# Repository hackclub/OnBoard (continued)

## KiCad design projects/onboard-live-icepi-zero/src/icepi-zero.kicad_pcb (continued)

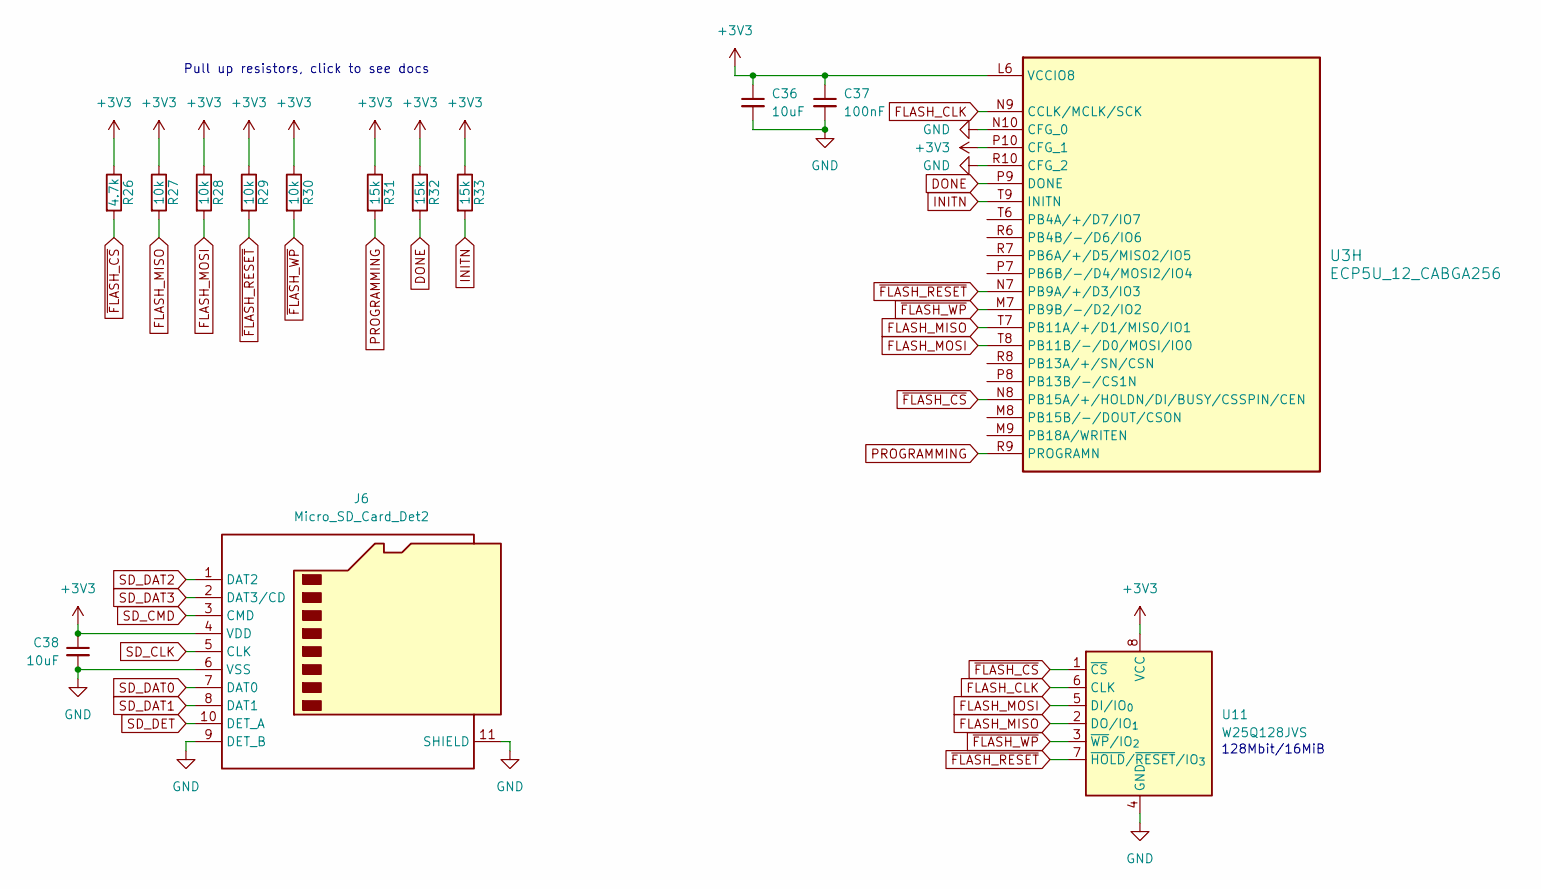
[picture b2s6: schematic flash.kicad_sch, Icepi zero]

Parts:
C36, C38: 10uF; C_0603_1608Metric
C37: 100nF; C_0402_1005Metric; JLCPCB Part # C307331
J6: Micro_SD_Card_Det2; microSD_HC_SOFNG_TF-008; JLCPCB Part # C428465
R26: 4.7k; R_0402_1005Metric; JLCPCB Part # C25900
R27, R28, R29, R30: 10k; R_0402_1005Metric; JLCPCB Part # C25744
R31, R32, R33: 15k; R_0402_1005Metric; JLCPCB Part # C25756
U3: ECP5U_12_CABGA256; BGA-256_14.0x14.0mm_Layout16x16_P0.8mm_Ball0.45mm_Pad0.32mm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; JLCPCB Part # C1521614
U11: W25Q128JVS; SOIC-8_5.3x5.3mm_P1.27mm; JLCPCB Part # C97521

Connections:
+3V3: C36.1, C37.1, C38.1, J6.4 (VDD), R26.1, R27.1, R28.1, R29.1, R30.1, R31.1, R32.1, R33.1, U3.L6 (VCCIO8), U3.P10 (CFG_1), U11.8 (VCC); also elsewhere on the board
DONE: R32.2, U3.P9 (DONE)
FLASH_CLK: U3.N9 (CCLK/MCLK/SCK), U11.6 (CLK)
FLASH_MISO: R27.2, U3.T7 (PB11A/+/D1/MISO/IO1), U11.2 (DO/IO_{1})
FLASH_MOSI: R28.2, U3.T8 (PB11B/-/D0/MOSI/IO0), U11.5 (DI/IO_{0})
GND: C36.2, C37.2, C38.2, J6.6 (VSS), J6.9 (DET_B), J6.11 (SHIELD), U3.N10 (CFG_0), U3.R10 (CFG_2), U11.4 (GND); also elsewhere on the board
INITN: R33.2, U3.T9 (INITN)
PROGRAMMING: R31.2, U3.R9 (PROGRAMN)
SD_CLK: J6.5 (CLK); also elsewhere on the board
SD_CMD: J6.3 (CMD); also elsewhere on the board
SD_DAT0: J6.7 (DAT0); also elsewhere on the board
SD_DAT1: J6.8 (DAT1); also elsewhere on the board
SD_DAT2: J6.1 (DAT2); also elsewhere on the board
SD_DAT3: J6.2 (DAT3/CD); also elsewhere on the board
SD_DET: J6.10 (DET_A); also elsewhere on the board
~FLASH_CS: R26.2, U3.N8 (PB15A/+/HOLDN/DI/BUSY/CSSPIN/CEN), U11.1 (~CS)
~FLASH_RESET: R29.2, U3.N7 (PB9A/+/D3/IO3), U11.7 (~HOLD/~RESET/IO_{3})
~FLASH_WP: R30.2, U3.M7 (PB9B/-/D2/IO2), U11.3 (~WP/IO_{2})

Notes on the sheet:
128Mbit/16MiB
Pull up resistors, click to see docs

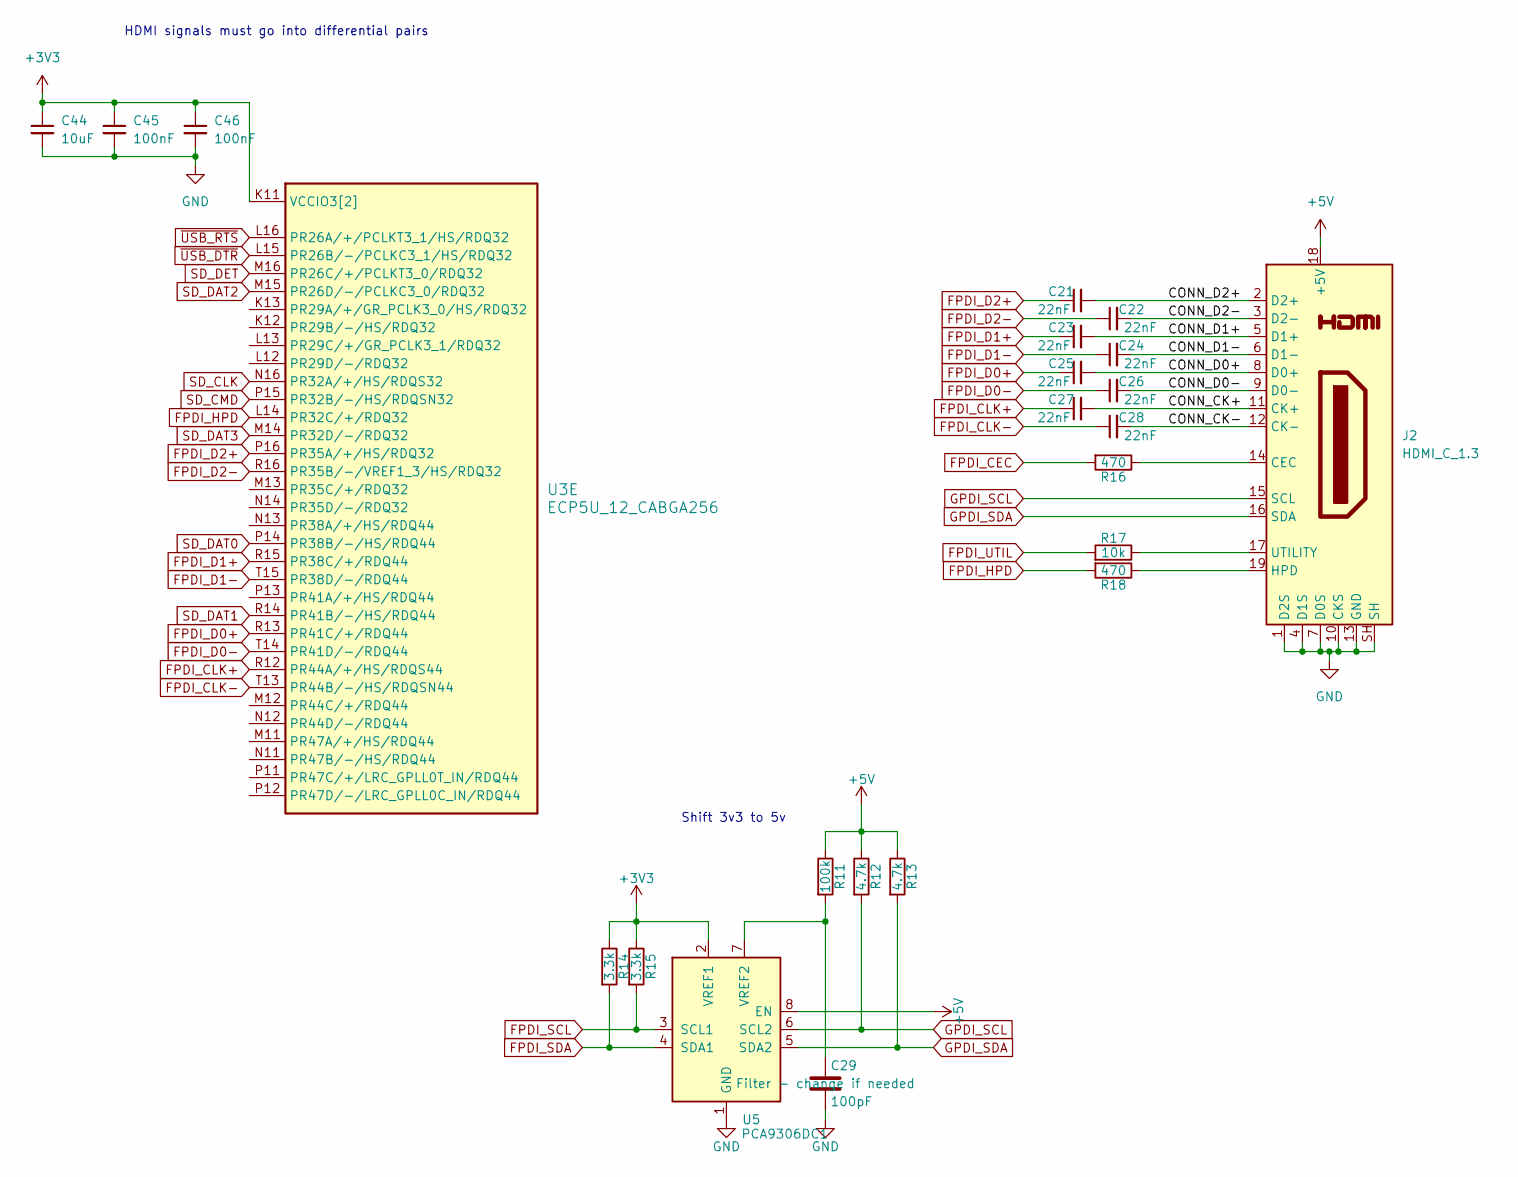
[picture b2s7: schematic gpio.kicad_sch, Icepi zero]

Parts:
C21, C22, C23, C24, C25, C26, C27, C28: 22nF; C_0402_1005Metric; JLCPCB Part # C1532
C29: 100pF; C_0402_1005Metric; JLCPCB Part # C1546
C44: 10uF; C_0603_1608Metric
C45, C46: 100nF; C_0402_1005Metric; JLCPCB Part # C307331
J2: HDMI_C_1.3; XKB Connection A71-05H4-111N1; JLCPCB Part # C2682170
R11: 100k; R_0402_1005Metric; JLCPCB Part # C25741
R12, R13: 4.7k; R_0402_1005Metric; JLCPCB Part # C25900
R14, R15: 3.3k; R_0402_1005Metric; JLCPCB Part # C25890
R16, R18: 470; R_0402_1005Metric; JLCPCB Part # C25117
R17: 10k; R_0402_1005Metric; JLCPCB Part # C25744
U3: ECP5U_12_CABGA256; BGA-256_14.0x14.0mm_Layout16x16_P0.8mm_Ball0.45mm_Pad0.32mm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; JLCPCB Part # C1521614
U5: PCA9306DC1; VSSOP-8_2.3x2mm_P0.5mm; JLCPCB Part # C129510

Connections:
+3V3: C44.1, C45.1, C46.1, R14.1, R15.1, U3.K11 (VCCIO3[2]), U3.L11 (VCCIO3[2]), U5.2 (VREF1); also elsewhere on the board
+5V: J2.18 (+5V), R11.1, R12.1, R13.1, U5.8 (EN); also elsewhere on the board
/GPIO/CONN_CK+: C27.2, J2.11 (CK+)
/GPIO/CONN_CK-: C28.2, J2.12 (CK-)
/GPIO/CONN_D0+: C25.2, J2.8 (D0+)
/GPIO/CONN_D0-: C26.2, J2.9 (D0-)
/GPIO/CONN_D1+: C23.2, J2.5 (D1+)
/GPIO/CONN_D1-: C24.2, J2.6 (D1-)
/GPIO/CONN_D2+: C21.2, J2.2 (D2+)
/GPIO/CONN_D2-: C22.2, J2.3 (D2-)
FPDI_CEC: R16.2; also elsewhere on the board
FPDI_CLK+: C27.1, U3.R12 (PR44A/+/HS/RDQS44)
FPDI_CLK-: C28.1, U3.T13 (PR44B/-/HS/RDQSN44)
FPDI_D0+: C25.1, U3.R13 (PR41C/+/RDQ44)
FPDI_D0-: C26.1, U3.T14 (PR41D/-/RDQ44)
FPDI_D1+: C23.1, U3.R15 (PR38C/+/RDQ44)
FPDI_D1-: C24.1, U3.T15 (PR38D/-/RDQ44)
FPDI_D2+: C21.1, U3.P16 (PR35A/+/HS/RDQ32)
FPDI_D2-: C22.1, U3.R16 (PR35B/-/VREF1_3/HS/RDQ32)
FPDI_HPD: R18.2, U3.L14 (PR32C/+/RDQ32)
FPDI_SCL: R15.2, U5.3 (SCL1); also elsewhere on the board
FPDI_SDA: R14.2, U5.4 (SDA1); also elsewhere on the board
FPDI_UTIL: R17.2; also elsewhere on the board
GND: C29.2, C44.2, C45.2, C46.2, J2.1 (D2S), J2.4 (D1S), J2.7 (D0S), J2.10 (CKS), J2.13 (GND), J2.SH, U5.1 (GND); also elsewhere on the board
GPDI_SCL: J2.15 (SCL), R12.2, U5.6 (SCL2)
GPDI_SDA: J2.16 (SDA), R13.2, U5.5 (SDA2)
unnamed: J2.14 (CEC), R16.1
unnamed: J2.19 (HPD), R18.1
unnamed: J2.17 (UTILITY), R17.1
unnamed: C29.1, R11.2, U5.7 (VREF2)
SD_CLK: U3.N16 (PR32A/+/HS/RDQS32); also elsewhere on the board
SD_CMD: U3.P15 (PR32B/-/HS/RDQSN32); also elsewhere on the board
SD_DAT0: U3.P14 (PR38B/-/HS/RDQ44); also elsewhere on the board
SD_DAT1: U3.R14 (PR41B/-/HS/RDQ44); also elsewhere on the board
SD_DAT2: U3.M15 (PR26D/-/PCLKC3_0/RDQ32); also elsewhere on the board
SD_DAT3: U3.M14 (PR32D/-/RDQ32); also elsewhere on the board
SD_DET: U3.M16 (PR26C/+/PCLKT3_0/RDQ32); also elsewhere on the board
~USB_DTR: U3.L15 (PR26B/-/PCLKC3_1/HS/RDQ32); also elsewhere on the board
~USB_RTS: U3.L16 (PR26A/+/PCLKT3_1/HS/RDQ32); also elsewhere on the board

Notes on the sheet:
Shift 3v3 to 5v
HDMI signals must go into differential pairs

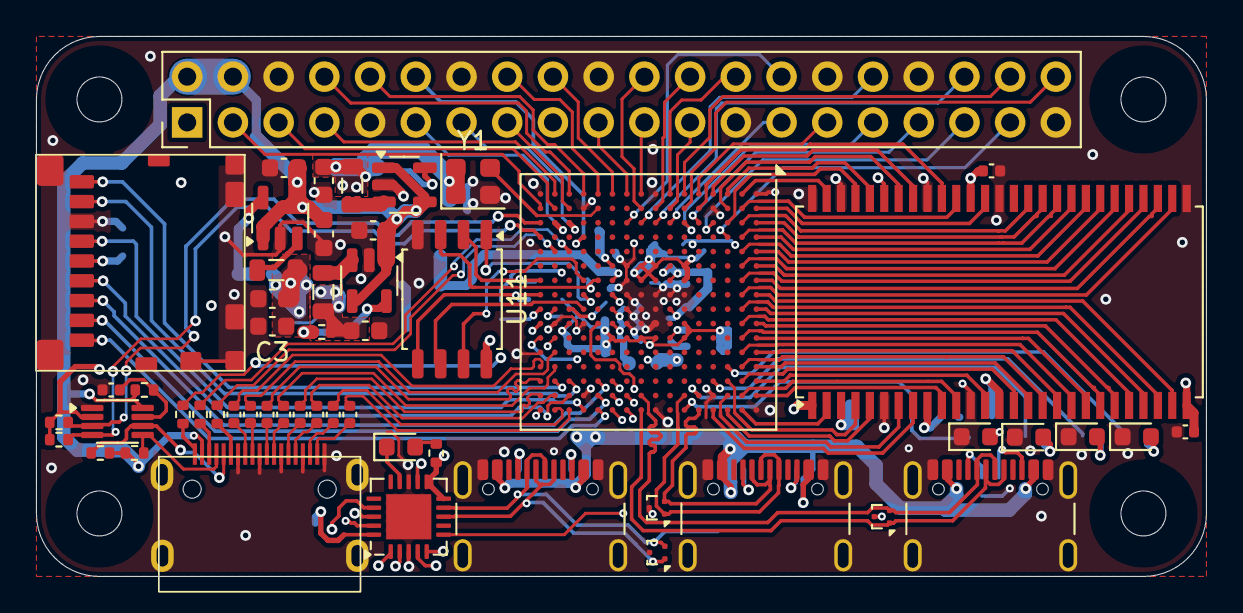
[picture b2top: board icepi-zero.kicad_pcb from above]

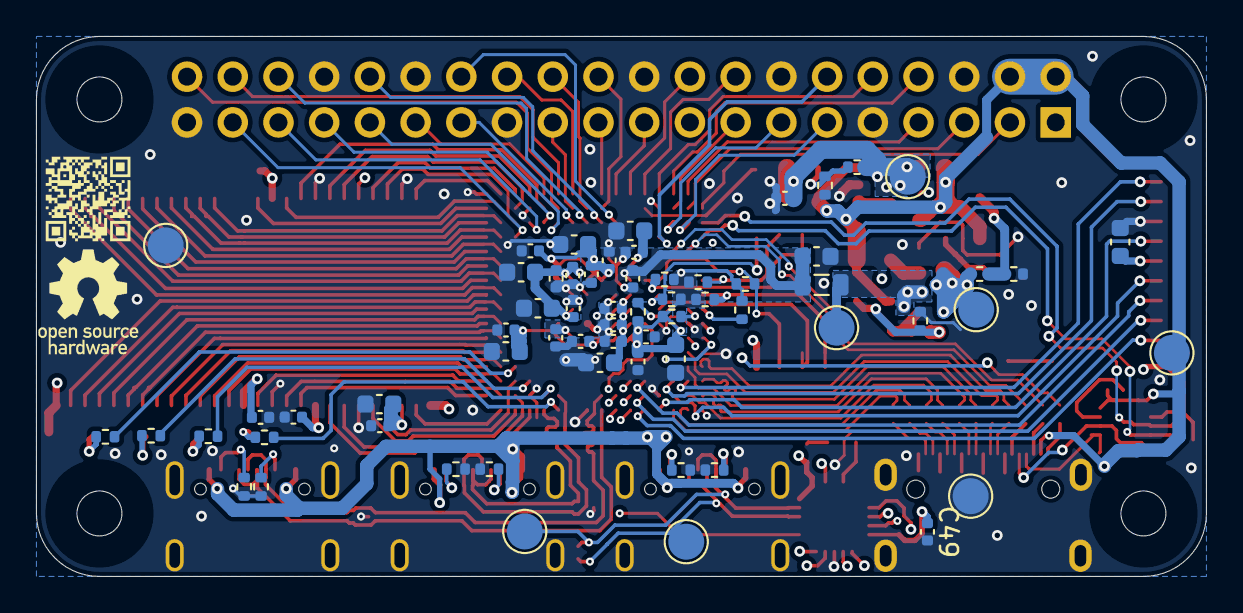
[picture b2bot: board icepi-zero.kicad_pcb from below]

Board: 4 copper layers, 65.0 x 30.0 mm, 121 parts (63 on the bottom side), 154 nets.

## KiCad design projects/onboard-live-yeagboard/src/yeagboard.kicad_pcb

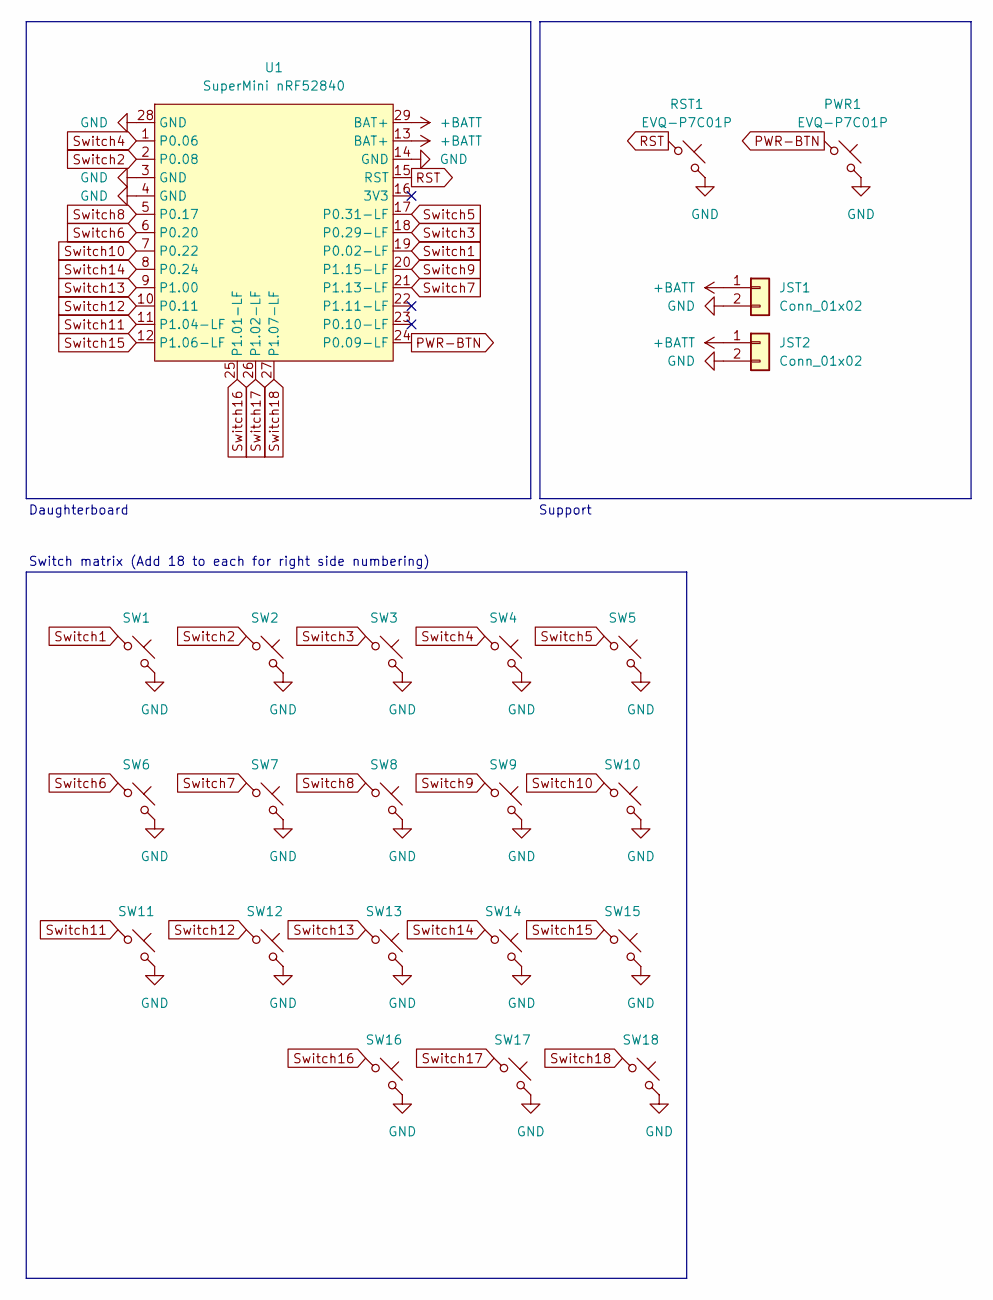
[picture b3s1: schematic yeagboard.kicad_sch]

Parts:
JST1, JST2: Conn_01x02; JST_PH_S2B-PH-K_1x02_P2.00mm_Horizontal
PWR1: EVQ-P7C01P; EVQ-P7C-Reversible
RST1: EVQ-P7C01P; EVQ-P7C-Reversible
SW1, SW2, SW3, SW4, SW5, SW6, SW7, SW8, SW9, SW10, SW11, SW12, SW13, SW14, SW15, SW16, SW17, SW18: SW_Push; Choc-V1-HS-Reversible
U1: SuperMini nRF52840; SuperMini_nRF52840_AH_Reversible

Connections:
+BATT: JST1.1, JST2.1, U1.13 (BAT+), U1.29 (BAT+)
GND: JST1.2, JST2.2, PWR1.2, RST1.2, SW1.2, SW2.2, SW3.2, SW4.2, SW5.2, SW6.2, SW7.2, SW8.2, SW9.2, SW10.2, SW11.2, SW12.2, SW13.2, SW14.2, SW15.2, SW16.2, SW17.2, SW18.2, U1.3 (GND), U1.4 (GND), U1.14 (GND), U1.28 (GND)
PWR-BTN: PWR1.1, U1.24 (P0.09-LF)
RST: RST1.1, U1.15 (RST)
Switch1: SW1.1, U1.19 (P0.02-LF)
Switch2: SW2.1, U1.2 (P0.08)
Switch3: SW3.1, U1.18 (P0.29-LF)
Switch4: SW4.1, U1.1 (P0.06)
Switch5: SW5.1, U1.17 (P0.31-LF)
Switch6: SW6.1, U1.6 (P0.20)
Switch7: SW7.1, U1.21 (P1.13-LF)
Switch8: SW8.1, U1.5 (P0.17)
Switch9: SW9.1, U1.20 (P1.15-LF)
Switch10: SW10.1, U1.7 (P0.22)
Switch11: SW11.1, U1.11 (P1.04-LF)
Switch12: SW12.1, U1.10 (P0.11)
Switch13: SW13.1, U1.9 (P1.00)
Switch14: SW14.1, U1.8 (P0.24)
Switch15: SW15.1, U1.12 (P1.06-LF)
Switch16: SW16.1, U1.25 (P1.01-LF)
Switch17: SW17.1, U1.26 (P1.02-LF)
Switch18: SW18.1, U1.27 (P1.07-LF)

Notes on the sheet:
Switch matrix (Add 18 to each for right side numbering)
Daughterboard
Support

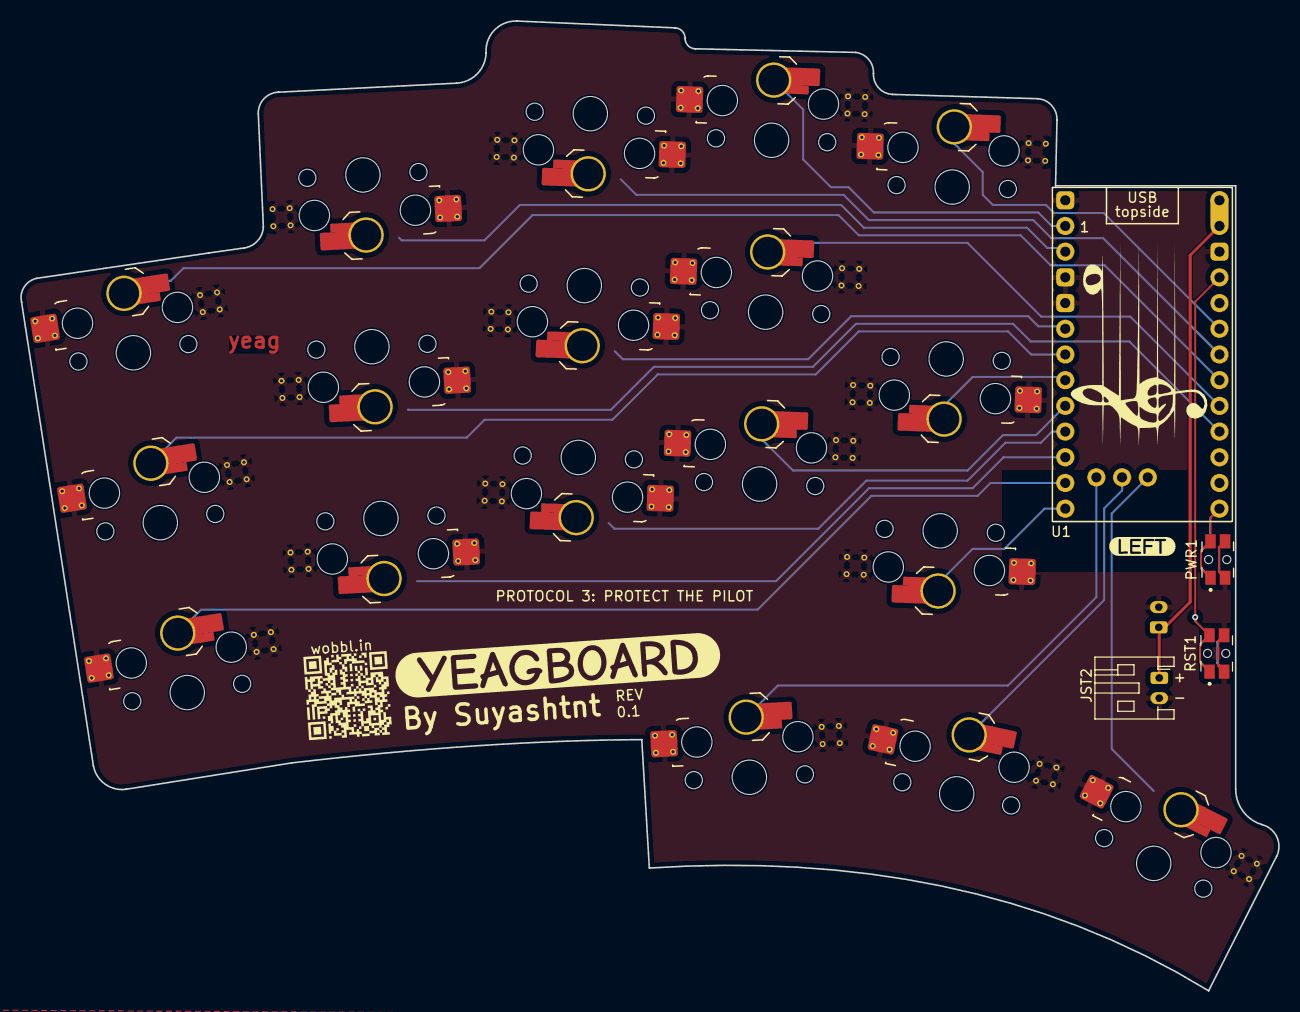
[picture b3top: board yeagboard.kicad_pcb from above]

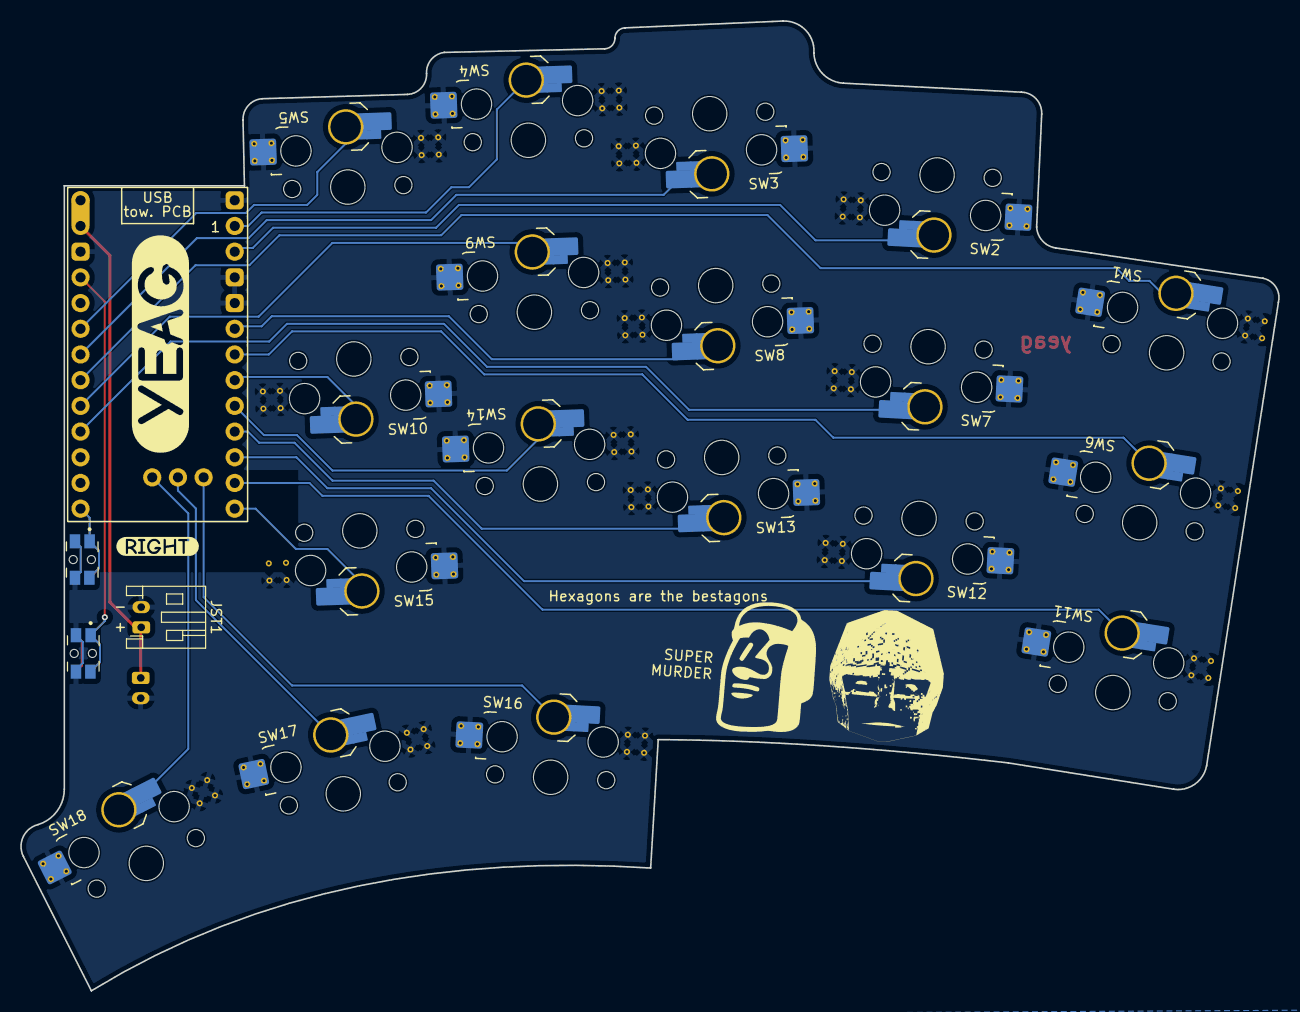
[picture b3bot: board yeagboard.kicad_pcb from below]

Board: 2 copper layers, 124.3 x 95.9 mm, 28 parts (21 on the bottom side), 22 nets.

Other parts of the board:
QR*****: WobblQR
kibuzzard-671E83A0: G***; kibuzzard-671E83A0
kibuzzard-671E83AE: G***; kibuzzard-671E83AE
kibuzzard-671E828F: G***; kibuzzard-671E828F
kibuzzard-671E8171: G***; kibuzzard-671E8171

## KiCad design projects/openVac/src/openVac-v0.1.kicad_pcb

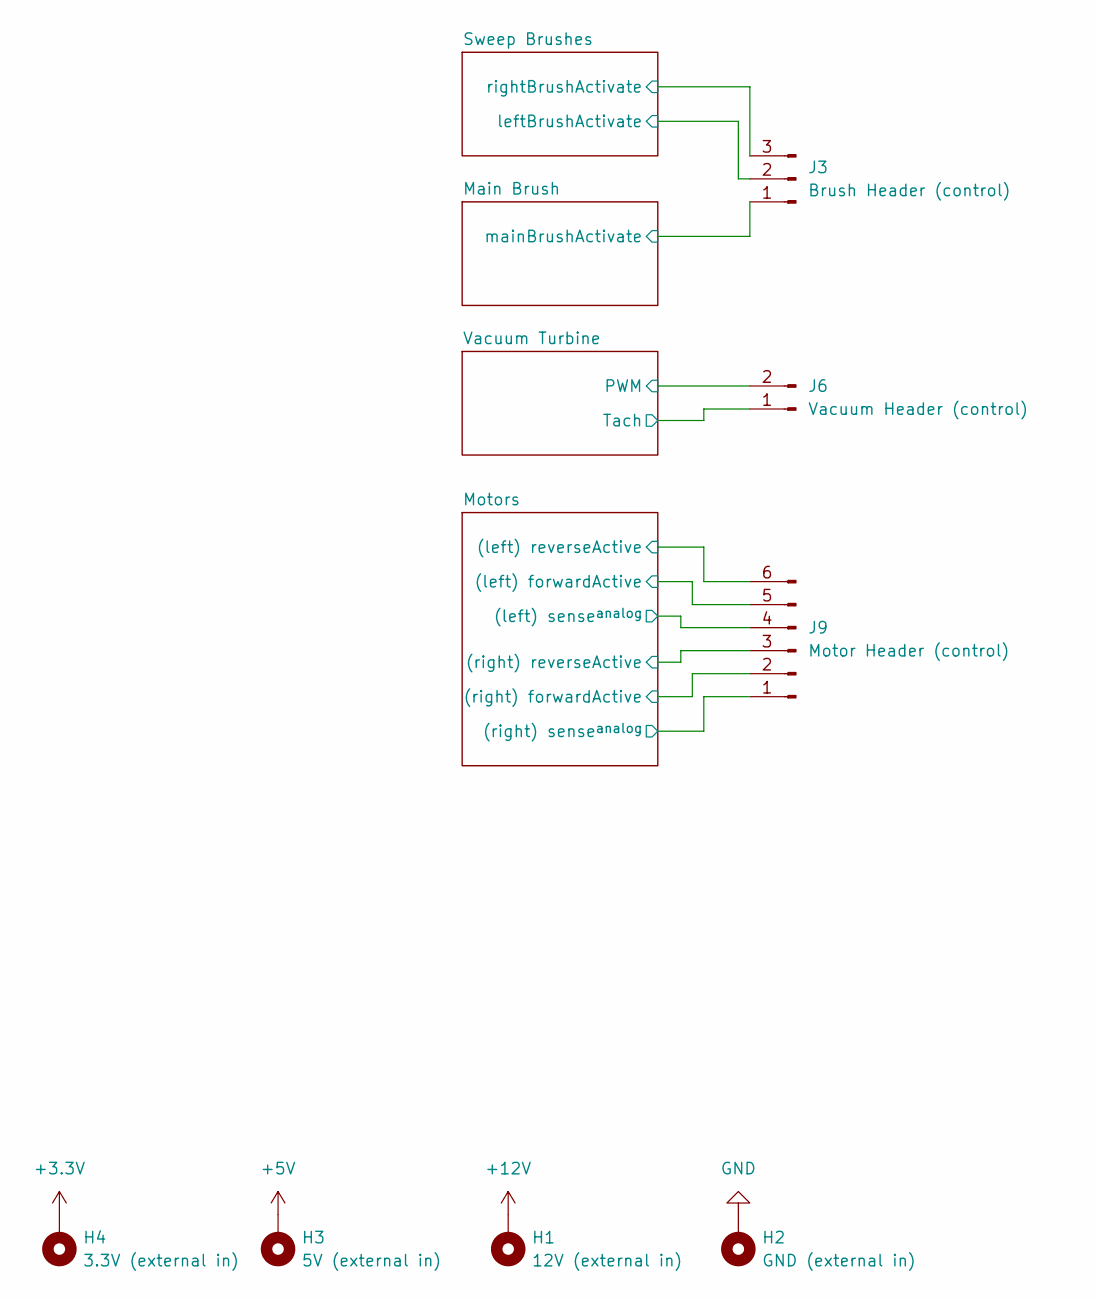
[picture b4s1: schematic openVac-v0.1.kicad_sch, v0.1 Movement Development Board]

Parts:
H1: 12V (external in); MountingHole_2.2mm_M2_DIN965_Pad
H2: GND (external in); MountingHole_2.2mm_M2_DIN965_Pad
H3: 5V (external in); MountingHole_2.2mm_M2_DIN965_Pad
H4: 3.3V (external in); MountingHole_2.2mm_M2_DIN965_Pad
J3: Brush Header (control); JST_PH_B3B-PH-K_1x03_P2.00mm_Vertical
J6: Vacuum Header (control); JST_PH_B2B-PH-K_1x02_P2.00mm_Vertical
J9: Motor Header (control); JST_PH_B6B-PH-K_1x06_P2.00mm_Vertical

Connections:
+3.3V: H4.1; also elsewhere on the board
+5V: H3.1; also elsewhere on the board
+12V: H1.1; also elsewhere on the board
/Main Brush/mainBrushActivate: J3.1; also elsewhere on the board
/Motors/(left) forwardActive: J9.5; also elsewhere on the board
/Motors/(left) reverseActive: J9.6; also elsewhere on the board
/Motors/(left) sense^{analog}: J9.4; also elsewhere on the board
/Motors/(right) forwardActive: J9.2; also elsewhere on the board
/Motors/(right) reverseActive: J9.3; also elsewhere on the board
/Motors/(right) sense^{analog}: J9.1; also elsewhere on the board
/Sweep Brushes/leftBrushActivate: J3.2; also elsewhere on the board
/Sweep Brushes/rightBrushActivate: J3.3; also elsewhere on the board
/Vacuum Turbine/PWM: J6.2; also elsewhere on the board
/Vacuum Turbine/Tach: J6.1; also elsewhere on the board
GND: H2.1; also elsewhere on the board

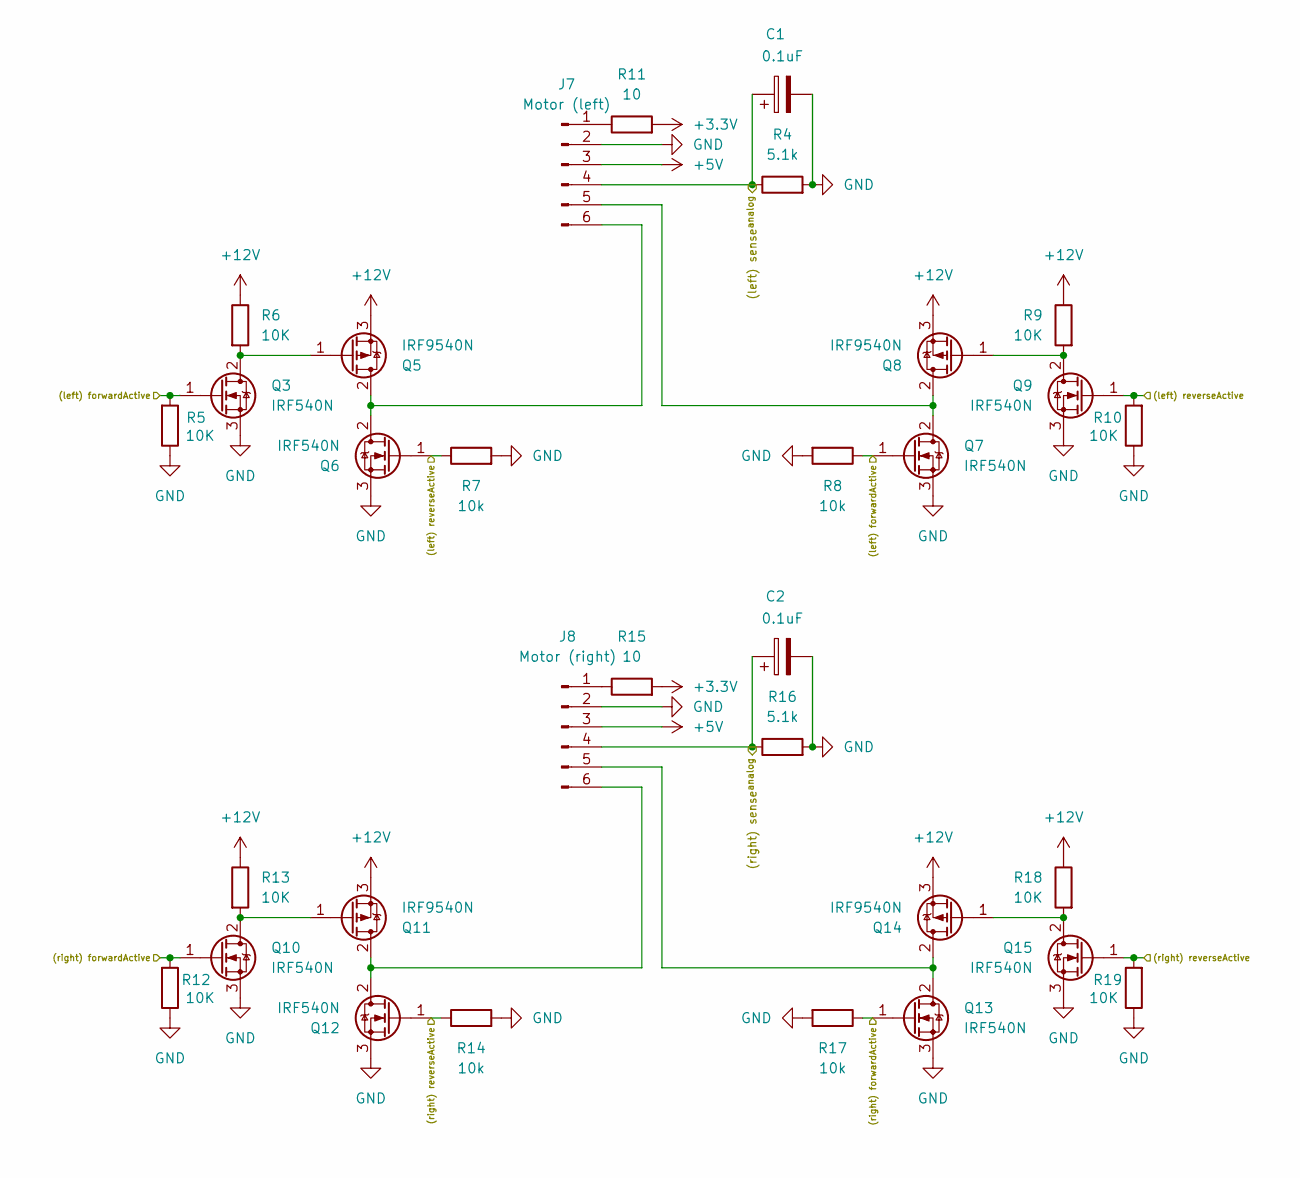
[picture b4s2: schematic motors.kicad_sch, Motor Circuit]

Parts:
C1, C2: 0.1uF; CP_Radial_D4.0mm_P1.50mm
J7: Motor (left); JST_PH_B6B-PH-K_1x06_P2.00mm_Vertical
J8: Motor (right); JST_PH_B6B-PH-K_1x06_P2.00mm_Vertical
Q3, Q6, Q7, Q9, Q10, Q12, Q13, Q15: IRF540N; TO-220-3_Vertical
Q5, Q8, Q11, Q14: IRF9540N; TO-220-3_Vertical
R4, R16: 5.1k; R_Axial_DIN0207_L6.3mm_D2.5mm_P10.16mm_Horizontal
R5, R6, R9, R10, R12, R13, R18, R19: 10K; R_Axial_DIN0207_L6.3mm_D2.5mm_P10.16mm_Horizontal
R7, R8, R14, R17: 10k; R_Axial_DIN0207_L6.3mm_D2.5mm_P10.16mm_Horizontal
R11, R15: 10; R_Axial_DIN0207_L6.3mm_D2.5mm_P10.16mm_Horizontal

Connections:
+3.3V: R11.2, R15.2; also elsewhere on the board
+5V: J7.3, J8.3; also elsewhere on the board
+12V: Q5.3 (S), Q8.3 (S), Q11.3 (S), Q14.3 (S), R6.1, R9.1, R13.1, R18.1; also elsewhere on the board
/Motors/(left) forwardActive: Q3.1 (G), Q7.1 (G), R5.2, R8.1; also elsewhere on the board
/Motors/(left) reverseActive: Q6.1 (G), Q9.1 (G), R7.1, R10.2; also elsewhere on the board
/Motors/(left) sense^{analog}: C1.1, J7.4, R4.1; also elsewhere on the board
/Motors/(right) forwardActive: Q10.1 (G), Q13.1 (G), R12.2, R17.1; also elsewhere on the board
/Motors/(right) reverseActive: Q12.1 (G), Q15.1 (G), R14.1, R19.2; also elsewhere on the board
/Motors/(right) sense^{analog}: C2.1, J8.4, R16.1; also elsewhere on the board
GND: C1.2, C2.2, J7.2, J8.2, Q3.3 (S), Q6.3 (S), Q7.3 (S), Q9.3 (S), Q10.3 (S), Q12.3 (S), Q13.3 (S), Q15.3 (S), R4.2, R5.1, R7.2, R8.2, R10.1, R12.1, R14.2, R16.2, R17.2, R19.1; also elsewhere on the board
unnamed: J7.1, R11.1
unnamed: J7.5, Q7.2 (D), Q8.2 (D)
unnamed: J7.6, Q5.2 (D), Q6.2 (D)
unnamed: J8.1, R15.1
unnamed: J8.5, Q13.2 (D), Q14.2 (D)
unnamed: J8.6, Q11.2 (D), Q12.2 (D)
unnamed: Q3.2 (D), Q5.1 (G), R6.2
unnamed: Q8.1 (G), Q9.2 (D), R9.2
unnamed: Q10.2 (D), Q11.1 (G), R13.2
unnamed: Q14.1 (G), Q15.2 (D), R18.2

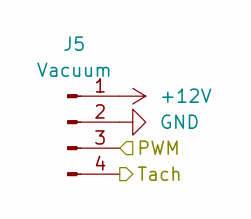
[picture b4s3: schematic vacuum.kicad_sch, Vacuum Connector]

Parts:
J5: Vacuum; JST_PH_B4B-PH-K_1x04_P2.00mm_Vertical

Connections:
+12V: J5.1; also elsewhere on the board
/Vacuum Turbine/PWM: J5.3; also elsewhere on the board
/Vacuum Turbine/Tach: J5.4; also elsewhere on the board
GND: J5.2; also elsewhere on the board

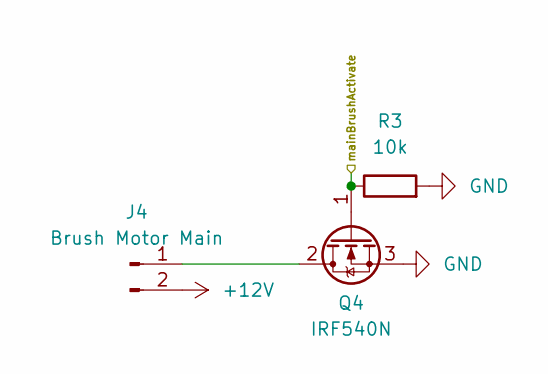
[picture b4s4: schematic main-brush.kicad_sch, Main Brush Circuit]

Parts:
J4: Brush Motor Main; JST_PH_B2B-PH-K_1x02_P2.00mm_Vertical
Q4: IRF540N; TO-220-3_Vertical
R3: 10k; R_Axial_DIN0207_L6.3mm_D2.5mm_P10.16mm_Horizontal

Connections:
+12V: J4.2; also elsewhere on the board
/Main Brush/mainBrushActivate: Q4.1 (G), R3.1; also elsewhere on the board
GND: Q4.3 (S), R3.2; also elsewhere on the board
unnamed: J4.1, Q4.2 (D)

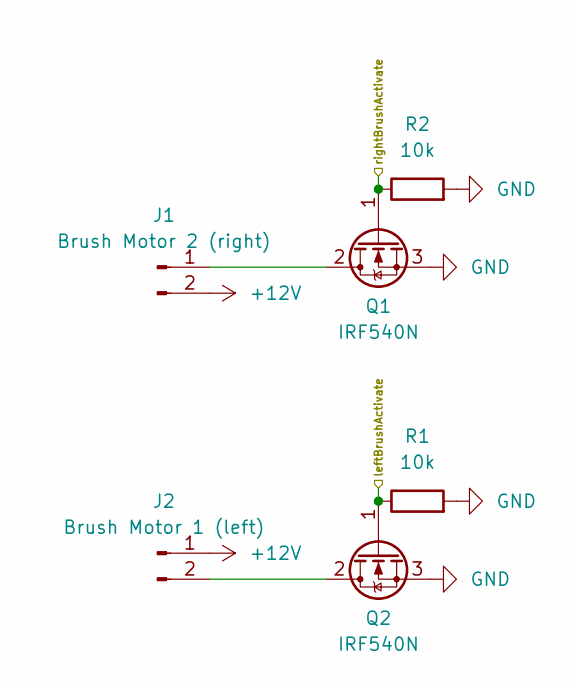
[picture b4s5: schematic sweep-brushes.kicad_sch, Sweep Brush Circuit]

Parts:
J1: Brush Motor 2 (right); JST_PH_B2B-PH-K_1x02_P2.00mm_Vertical
J2: Brush Motor 1 (left); JST_PH_B2B-PH-K_1x02_P2.00mm_Vertical
Q1, Q2: IRF540N; TO-220-3_Vertical
R1, R2: 10k; R_Axial_DIN0207_L6.3mm_D2.5mm_P10.16mm_Horizontal

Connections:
+12V: J1.2, J2.1; also elsewhere on the board
/Sweep Brushes/leftBrushActivate: Q2.1 (G), R1.1; also elsewhere on the board
/Sweep Brushes/rightBrushActivate: Q1.1 (G), R2.1; also elsewhere on the board
GND: Q1.3 (S), Q2.3 (S), R1.2, R2.2; also elsewhere on the board
unnamed: J1.1, Q1.2 (D)
unnamed: J2.2, Q2.2 (D)

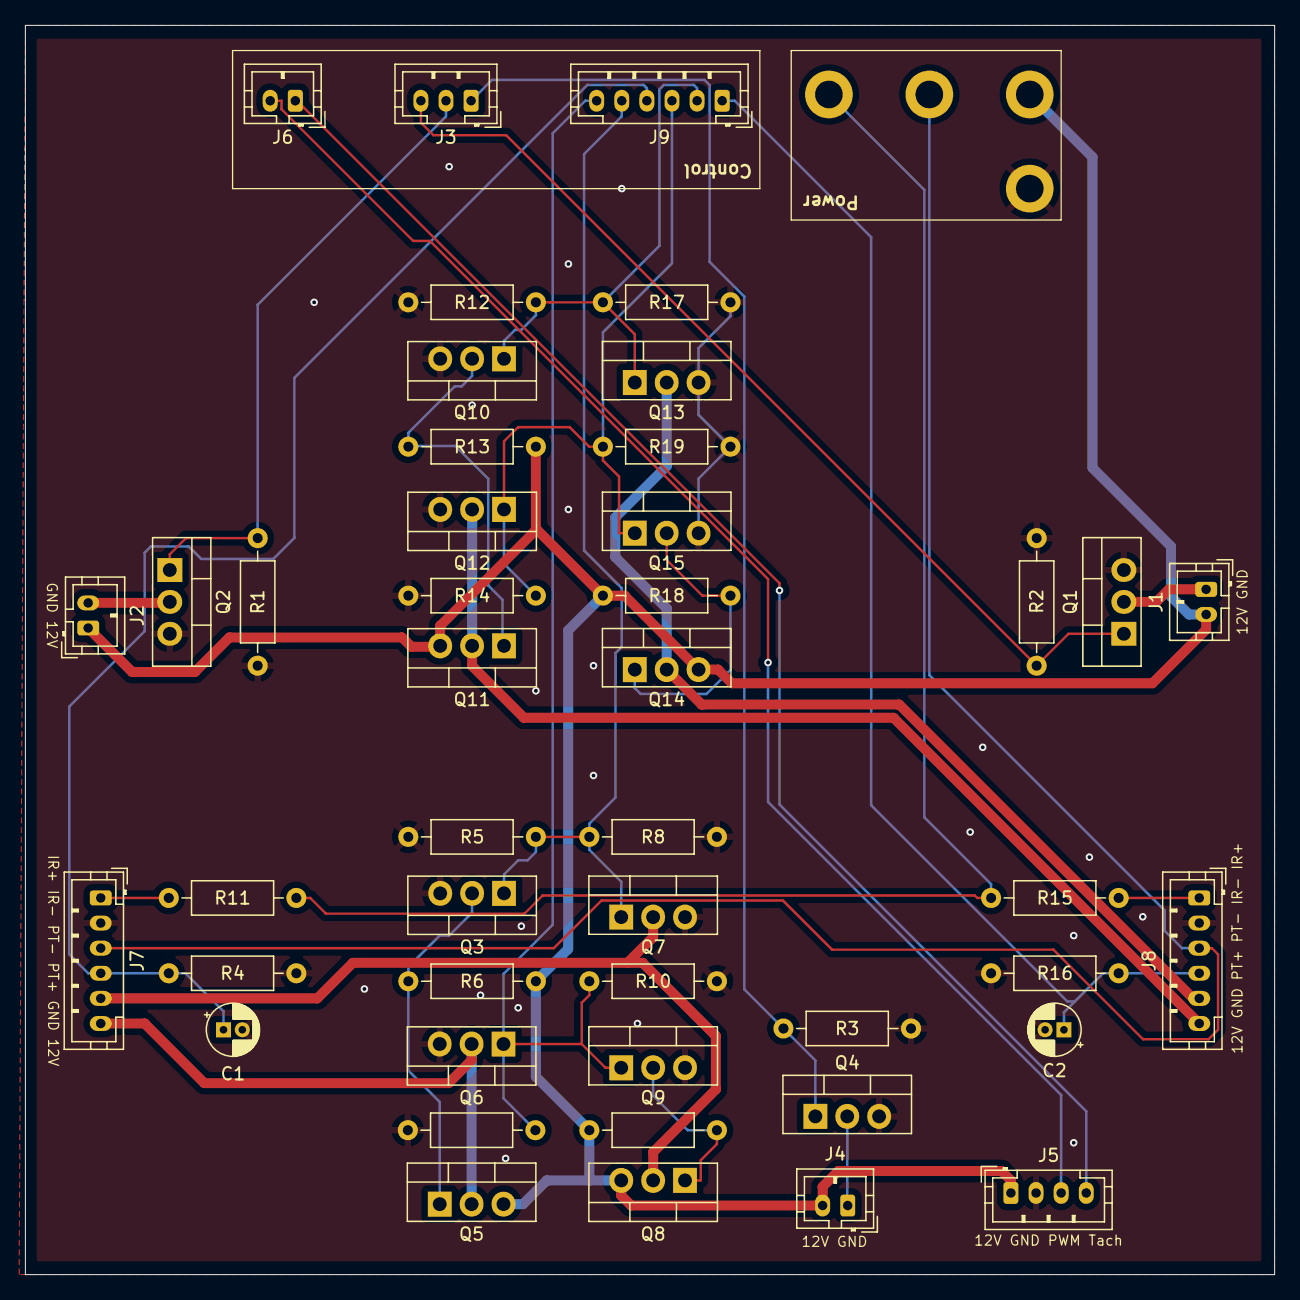
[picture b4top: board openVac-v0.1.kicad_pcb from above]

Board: 2 copper layers, 99.5 x 99.5 mm, 49 parts (0 on the bottom side), 28 nets.
